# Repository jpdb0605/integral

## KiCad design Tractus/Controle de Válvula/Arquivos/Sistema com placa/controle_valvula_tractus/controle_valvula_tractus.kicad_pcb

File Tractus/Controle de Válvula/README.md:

# Sistema de Controle da Válvula - Tractus
A ideia desse sistema é automatizar o controle do fluxo de água no acoplamento dos transdutores do TRACTUS, substituindo o controle manual. Para isso, é necessário que o sistema faça uma leitura do fluxo de água, processe esse sinal e retorne o comando à válvula proporcional, fazendo-a abrir ou fechar, de acordo com o nível de fluxo desejado.

Para o projeto, os componentes utilizados serão:
- [Fusível PTC 2.5A]()
- [Potenciômetro Linear 10K + Knob](https://www.eletrogate.com/potenciometro-linear-10k?utm_source=Site&utm_medium=GoogleMerchant&utm_campaign=GoogleMerchant&gad_source=4&gad_campaignid=20223015315&gbraid=0AAAAADqxjs_gpqOJfLVmq1WIuAi4hx24R&gclid=CjwKCAjwqJXUBhBNEiwA8BgG7omOoSZQO_TGoV6BXl1_1kDrA87dErBUL3YU2gr2WFoq7l1gJ6wrxxoCuWoQAvD_BwE)
- [Display ST7735 SPI]()
- [Chave Gangorra]()
- [Botão Cogumelo]() 
- [LED RGB]()
- [Conector para fonte]()
- [Conector de aviação 7 ou 8 pin para válvula (gx16)]()
- [espaçadores de nylon + parafusos m3]()
- [Conexões hidráulicas para sensor e válvula]()

[toc]
## **Renesas R7FA4M1AB3CFM_AA0**

Esse chip de microcontrolador foi selecionado pois é o mesmo chip usado no Arduino R4 Minima, que seria utilizado anteriormente, mas foi substituído quando a decisão da placa foi adotada. Ele tem um pino DAC, usado para enviar o sinal para o controle da válvula. Os outros pinos GPIO serão usados para os demais componentes.
[Datasheet](https://www.renesas.com/en/document/dst/ra4m1-group-datasheet?r=1054146)
[Manual de usuário](https://www.renesas.com/en/document/mah/renesas-ra4m1-group-users-manual-hardware?r=1054146)
- Corrente máxima: 8.3mA
- Alimentação: 3.3V
- Pino DAC

## **Válvula Proporcional de Esfera Motorizada 1/2"**
A válvula funciona com uma esfera motorizada, que é movida para abrir ou fechá-la e controlar o fluxo. 
Nesse caso, quando a tensão for de 0V, a válvula está totalmente fechada e, quando a tensão for de 10V, está totalmente aberta.

Ela foi escolhida por ser uma válvula proporcional, alimentada por 12V (tensão da fonte), tem tamanho de 1/2" e é de fácil controle.

Essa válvula também tem um fio de saída, que determina para o microcontrolador a posição atual da esfera. Não está sendo utilizado no momento.

O microcontrolador só é capaz de fornecer 3.3V. Portanto, um amplificador operacional foi adotado para amplificar o sinal analógico, dando um ganho de 3.
- Alimentação: 12V
- Entrada: Sinal de 0 a 10V proveniente do amplificador operacional
- Saída: Sinal que diz a posição da esfera motorizada
- Corrente de Pico: 950mA

[Link](https://simokit.com.br/product/valvula-esfera-reta-inox-dn15-proporcional-0-10v/)

## **Sensor de Fluxo YF-B1**
Esse sensor de Fluxo de Água se adequa ao projeto pelo tamanho do tubo (1/2"), equivalente ao tubo já utilizado para o projeto, e pela vazão medida, que vai de 1L/min a 25L/min. O fluxo máximo medido pela empresa foi de cerca de 20L/min, então não haveria problemas de o fluxo real superar a capacidade de medição do sensor.

O sensor é composto por uma turbina, um ímã e um sensor hall. Quando a água passa pelo sensor, a turbina é girada e o ímã gera um campo magnético, medido pelo sensor hall e convertido em sinal elétrico, na forma de uma onda quadrada, com amplitude (Vpp) igual à alimentação. O fluxo é medido pela contagem de pulsos (frequência), dividido por 11.
- Corrente máxima: 15mA
- Alimentação: 5-15V
- Q = F/11

[Link](https://www.smartcomponentes.com/produto/sensor-de-fluxo-de-agua-12-1-25lmin-latao-yf-b1-175mpa.html)
[Datasheet](https://www.berrybase.de/en/product-datasheet/019391e394b77123b67497a442305b7e/create?srsltid=AfmBOop15xInDI9Svvvt8oZdoz8aRe0pngtSfpSjBk5hLPy-z7e2IX37)

## **Amplificador Operacional TLV2372**
Esse chip tem dois amplificadores operacionais dentro de si, que serão utilizados para funções diferentes.

O primeiro é utilizado para dar ganho ao sinal de saída do controlador para a válvula. Ele está conectado em configuração não inversora e tem ganho a partir da seguinte relação:

No caso, os resistores em questão são R6 e R3. O sinal vem do pino 53 do microcontrolador. 
O resistor R7 é um resistor de pulldown para drenar a corrente e forçar a saída a ser 0V, evitando que haja sinal quando não deveria.

O segundo amplificador está sendo utilizado como um buffer entre o sensor de fluxo e o microcontrolador. O divisor de tensão da entrada reduz a tensão de 12V para 3.3V, que passa pelo buffer e dá a saída no pino 49 do microcontrolador.
O resistor R13 atua como proteção, limitando a corrente e reduzindo o atraso introduzido pelas capacitâncias parasitas do circuito.

## **Regulador de Tensão 3.3V AMS1117-3.3**
O regulador está no circuito para baixar a tensão de 12V para 3.3V, que é usada para alimentar alguns componentes. Os capacitores são um circuito auxiliar exigido pelo datasheet do regulador e servem para fazer a filtragem de variações de baixas e altas potências.

[Link]()

## **LED RGB**
Usado para exibir visualmente o estado do sistema, com cada cor tendo um significado diferente:
- Azul:
- Amarelo:
- Vermelho:
- Laranja:
Eles são conectados ao microcontrolador pelos pinos 12 (RED), 13 (BLUE), 14 (GREEN).

## Fonte
https://www.fontesmeanwell.com.br/rs-35-12-fonte-chaveada-fechada-36w-88-264vca125-373vcc-saida-12v-3a-mean-well
- (99x82x36)mm

## Display ST7735

## Conector USB-C 2.0
Usado para passar o código ao microcontrolador.

## BOM
- 7x Capacitor Cerâmico smd 100nF
- 1x Capacitor Cerâmico smd 22uF
- 1x Capacitor Cerâmico smd 10uF
- 2x Capacitor Cerâmico smd 4.7uF
- 6x Resistor smd 10k
- 2x Resistor smd 20k
- 2x Resistor smd 1k
- 2x Resistor smd 5.1k
- 3x Resistor smd 330
- 1x Resistor smd 30k
- 1x Fusível PTC smd 2.5A
- 2x Botão Push smd
- 1x LED RGB catodo comum
- 1x Conector Fêmea USB-C 2.0
- 1x Conector Molex Mini-Fit Jr 2x4
- 1x Conector Molex Mini-Fit Jr 2x3
- 1x Conector Molex Mini-Fit Jr 2x2
- 1x Botão Cogumelo
- 1x Chave Gangorra On-Off
- 1x TLV2372
- 1x AMS1117-3.3
- 1x YF-B1
- 1x Potenciômetro Linear 10k
- 1x Knob de potenciômetro
- 1x Válvula Proporcional
- 1x Renesas R7FA4M1AB3CFM_AA0
- 1x Fonte RS-35-12
- 1x Conector de Tomada Tripolar Macho
- 1x Conectores de Aviação GX16 7 pinos
- ?x componentes de fixação mecânica

## **Modelos 3D**
- [Potenciômetro](https://sketchfab.com/3d-models/potenciometro-linear-10k-ee4e9d38fba44a51ad0ec0225995b813)
- [Knob](https://www.traceparts.com/br/product/rs-group-knob-black-blue-marker-line-6mm-d?CatalogPath=RS_COMPONENTS%3APSF_433042&Product=90-08032024-083055)
- [Display](https://grabcad.com/library/tft-lcd-1-8-inch-spi-st7735-128x160-1)
- [LED RGB](https://sketchfab.com/3d-models/rgb-led-7ee14ba4a6204e74a5d37169f342c785)
- [Fonte - não encontrado]()
- [Botão de Emergência - não encontrado]()
- [Chave Gangorra On-Off - não encontrado]()
- [Conector Tomada Tripolar Macho](https://grabcad.com/library/tomada-macho-2p-t-10a-250v-1)
- [Conector de Aviação GX16 - 7 ou 8 Pinos - não encontrado]()

## **Consumo de Corrente**

## Esquemático

## Controle
No código, é feita a contagem de pulsos vindos do sensor para determinar o fluxo. A partir disso, a ideia é definir o valor de máximo do fluxo quando a válvula está 100% aberta e definir o valor desejado do fluxo. Após isso, o fluxo será definido por uma conversão digital-analógico de valor até 3.3V. Esse sinal passa por um amplificador operacional de ganho 3 e segue para a válvula.

## Diagrama Lógico

## Diagrama de Potência

## Diagrama do Código

## Requisição de Compras
[RC Válvula](https://integralmonitoramentoein138-my.sharepoint.com/:x:/g/personal/joao_baptista_integral-imi_com_br/IQAJ0VLL1GrMQLJxgtgs7qGfAQLTgIY3VIOuGB1zUlPJKKM?e=Wh28EZ)
[RC Sensor](https://integralmonitoramentoein138-my.sharepoint.com/:x:/g/personal/joao_baptista_integral-imi_com_br/IQDEU0ApyflLTq0Ow4kNu74WAR9PTYG0pupGPaK7aSaTUOs?e=R4D45n)

## Testes
1) Teste de Continuidade entre alimentação e terra, pinos do microcontrolador e componentes.
2) Com a válvula desconectada, ligar o sistema pela chave e medir a tensão da fonte (aproximadamente 12V).
3) Testar o display e verificar sua mensagem.
4) Girar o potenciômetro e testar a variação do Set no display e a variação das cores do LED.
5) Pressionar o botão de Stop e verificar o display e o LED. Depois soltar o botão e ver se o sistema retorna ao estado normal.
6) Testar a turbina do sensor e verificar o display e o LED.
7) Medir a tensão de saída do amplificador operacional, onde o mínimo deve ser 0V e o máximo deve ser 10V (~9.99V).
8) Conectar a válvula no sistema e girar o potenciômetro para verificar se o controle está sendo efetuado.

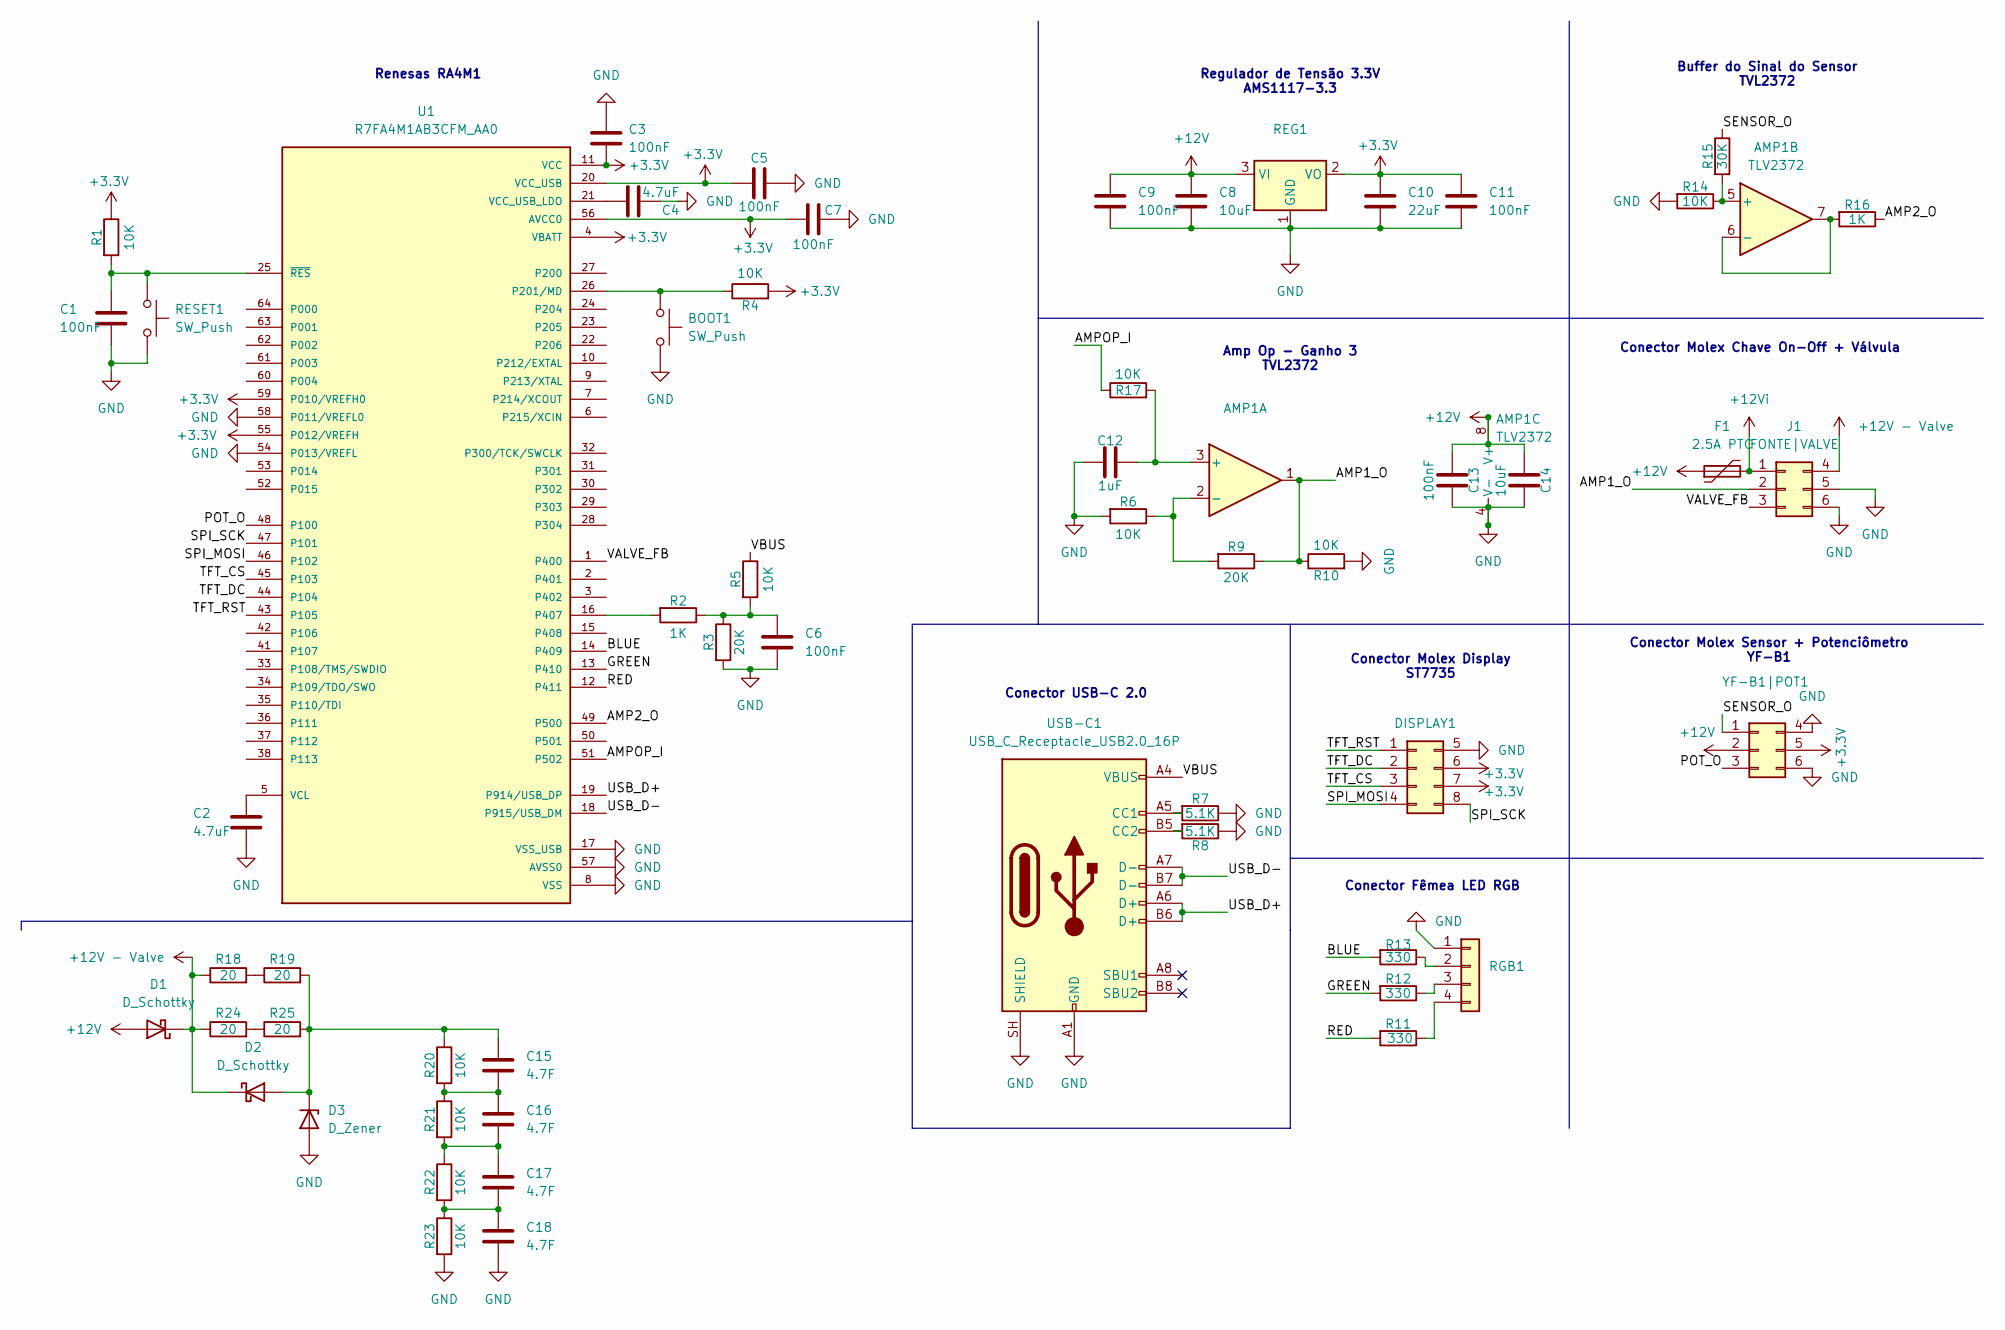
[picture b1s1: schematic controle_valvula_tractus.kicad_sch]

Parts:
AMP1: TLV2372; SOIC-8_3.9x4.9mm_P1.27mm
BOOT1: SW_Push; SW_SPST_B3U-1000P
C1, C3, C5, C6, C7, C9, C13: 100nF; C_0603_1608Metric
C2, C4: 4.7uF; C_0603_1608Metric
C8: 10uF; C_0805_2012Metric
C10: 22uF; C_0805_2012Metric
C11: 100nF; C_0805_2012Metric
C12: 1uF; C_0603_1608Metric
C14: 10uF; C_1206_3216Metric
C15, C16, C17, C18: 4.7F; C_Radial_D12.5mm_H20.0mm_P5.00mm
D1, D2: D_Schottky; D_SMC
D3: D_Zener; D_SMA
DISPLAY1: Conn_02x04_Top_Bottom; Molex_Mini-Fit_Jr_5566-08A_2x04_P4.20mm_Vertical
F1: 2.5A PTC; Fuse_1812_4532Metric
J1: FONTE|VALVE; Molex_Mini-Fit_Jr_5566-06A_2x03_P4.20mm_Vertical
R1, R4, R5, R6, R10, R14, R17, R20, R21, R22, R23: 10K; R_0603_1608Metric
R2, R16: 1K; R_0603_1608Metric
R3, R9: 20K; R_0603_1608Metric
R7, R8: 5.1K; R_0603_1608Metric
R11, R12, R13: 330; R_0603_1608Metric
R15: 30K; R_0603_1608Metric
R18, R19, R24, R25: 20; R_2512_6332Metric
REG1: AMS1117-3.3; SOT-223-3_TabPin2
RESET1: SW_Push; SW_SPST_B3U-1000P
RGB1: Conn_01x04; PinSocket_1x04_P2.54mm_Vertical
U1: R7FA4M1AB3CFM_AA0; QFP50P1200X1200X170-64N; PARTREV 1.1
USB-C1: USB_C_Receptacle_USB2.0_16P; USB_C_Receptacle_HRO_TYPE-C-31-M-12
YF-B1|POT1: Conn_02x03_Top_Bottom; Molex_Mini-Fit_Jr_5566-06A_2x03_P4.20mm_Vertical

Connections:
+3.3V: C3.1, C5.1, C7.1, C10.1, C11.1, DISPLAY1.6, DISPLAY1.7, R1.1, R4.2, REG1.2 (VO), U1.4 (VBATT), U1.11 (VCC), U1.20 (VCC_USB), U1.39 (VCC), U1.55 (P012/VREFH), U1.56 (AVCC0), U1.59 (P010/VREFH0), YF-B1|POT1.5
+12V: AMP1.8 (V+), C8.1, C9.1, C13.1, C14.1, D1.2 (A), F1.1, REG1.3 (VI), YF-B1|POT1.2
+12V - Valve: D1.1 (K), D2.1 (K), J1.4, R18.1, R24.1
+12Vi: F1.2, J1.1
/AMP1_O: AMP1.1, J1.2, R9.1, R10.1
/AMP2_O: R16.1, U1.49 (P500)
/AMPOP_I: R17.1, U1.51 (P502)
/BLUE: R13.2, U1.14 (P409)
/GREEN: R12.2, U1.13 (P410)
/POT_O: U1.48 (P100), YF-B1|POT1.3
/RED: R11.2, U1.12 (P411)
/SENSOR_O: R15.1, YF-B1|POT1.1
/SPI_MOSI: DISPLAY1.4, U1.46 (P102)
/SPI_SCK: DISPLAY1.8, U1.47 (P101)
/TFT_CS: DISPLAY1.3, U1.45 (P103)
/TFT_DC: DISPLAY1.2, U1.44 (P104)
/TFT_RST: DISPLAY1.1, U1.43 (P105)
/USB_D+: U1.19 (P914/USB_DP), USB-C1.A6 (D+), USB-C1.B6 (D+)
/USB_D-: U1.18 (P915/USB_DM), USB-C1.A7 (D-), USB-C1.B7 (D-)
/VALVE_FB: J1.3, U1.1 (P400)
/VBUS: R5.1, USB-C1.A4 (VBUS), USB-C1.A9 (VBUS), USB-C1.B4 (VBUS), USB-C1.B9 (VBUS)
GND: AMP1.4 (V-), BOOT1.2, C1.1, C2.2, C3.2, C4.2, C5.2, C6.2, C7.2, C8.2, C9.2, C10.2, C11.2, C12.1, C13.2, C14.2, C18.2, D3.2 (A), DISPLAY1.5, J1.5, J1.6, R3.2, R6.2, R7.1, R8.1, R10.2, R14.2, R23.2, REG1.1 (GND), RESET1.2, RGB1.1, U1.8 (VSS), U1.17 (VSS_USB), U1.40 (VSS), U1.54 (P013/VREFL), U1.57 (AVSS0), U1.58 (P011/VREFL0), USB-C1.A1 (GND), USB-C1.A12 (GND), USB-C1.B1 (GND), USB-C1.B12 (GND), USB-C1.SH (SHIELD), YF-B1|POT1.4, YF-B1|POT1.6
unnamed: AMP1.3 (+), C12.2, R17.2
unnamed: AMP1.2 (-), R6.1, R9.2
unnamed: AMP1.5 (+), R14.1, R15.2
unnamed: AMP1.6 (-), AMP1.7, R16.2
unnamed: C6.1, R2.1, R3.1, R5.2
unnamed: C15.2, C16.1, R20.2, R21.1
unnamed: C16.2, C17.1, R21.2, R22.1
unnamed: C17.2, C18.1, R22.2, R23.1
unnamed: C15.1, D2.2 (A), D3.1 (K), R19.2, R20.1, R25.2
unnamed: R18.2, R19.1
unnamed: R24.2, R25.1
unnamed: R13.1, RGB1.2
unnamed: R12.1, RGB1.3
unnamed: R11.1, RGB1.4
unnamed: BOOT1.1, R4.1, U1.26 (P201/MD)
unnamed: R2.2, U1.16 (P407)
unnamed: C4.1, U1.21 (VCC_USB_LDO)
unnamed: C2.1, U1.5 (VCL)
unnamed: C1.2, R1.2, RESET1.1, U1.25 (~RES)
unnamed: R7.2, USB-C1.A5 (CC1)
unnamed: R8.2, USB-C1.B5 (CC2)

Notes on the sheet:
Conector Molex Display ST7735
Buffer do Sinal do Sensor TVL2372
Conector USB-C 2.0
Conector Molex Sensor + Potenciômetro YF-B1
Conector Molex Chave On-Off + Válvula
Renesas RA4M1
Conector Fêmea LED RGB
Amp Op - Ganho 3 TVL2372
Regulador de Tensão 3.3V AMS1117-3.3

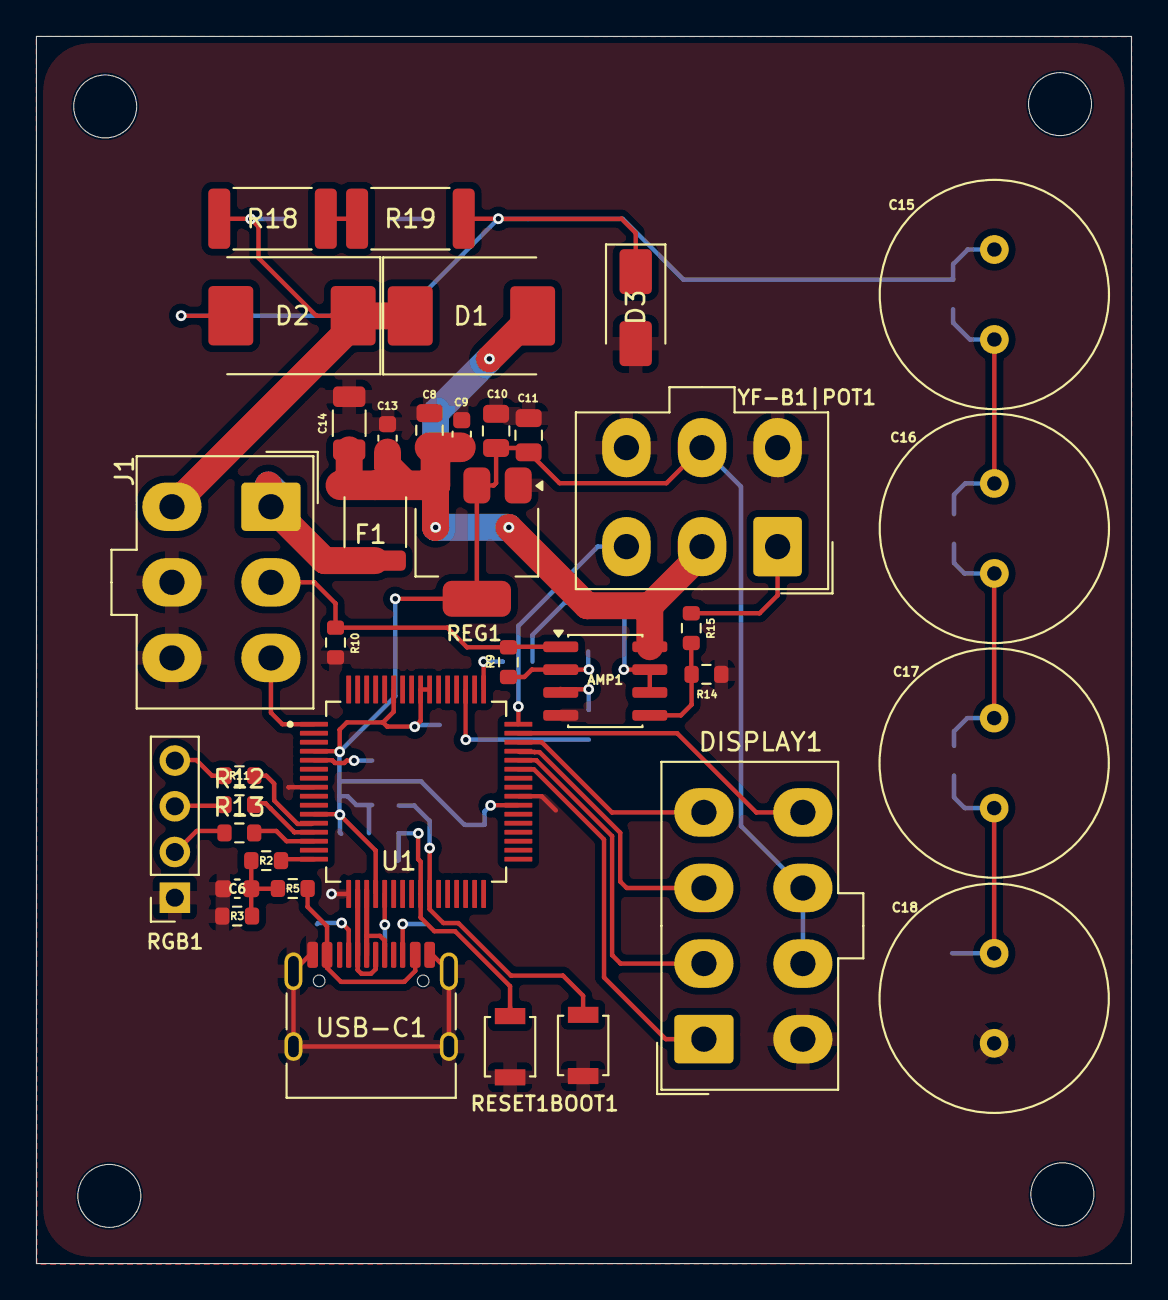
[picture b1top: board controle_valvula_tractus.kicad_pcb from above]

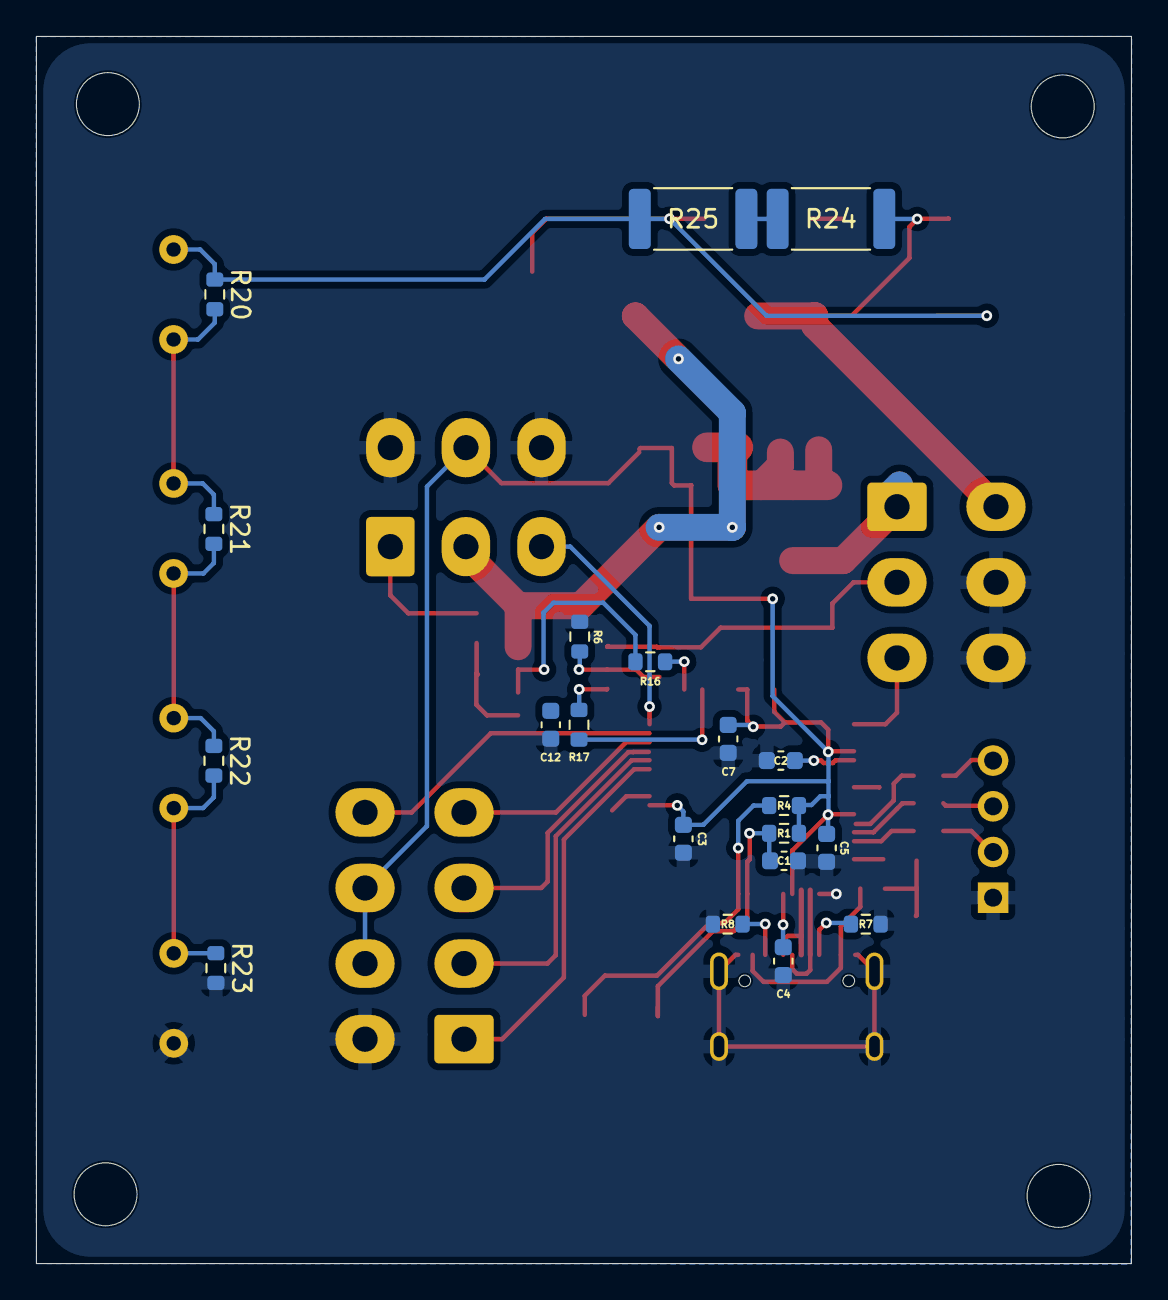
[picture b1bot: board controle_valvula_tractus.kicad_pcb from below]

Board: 2 copper layers, 60.9 x 68.2 mm, 57 parts (20 on the bottom side), 43 nets.
